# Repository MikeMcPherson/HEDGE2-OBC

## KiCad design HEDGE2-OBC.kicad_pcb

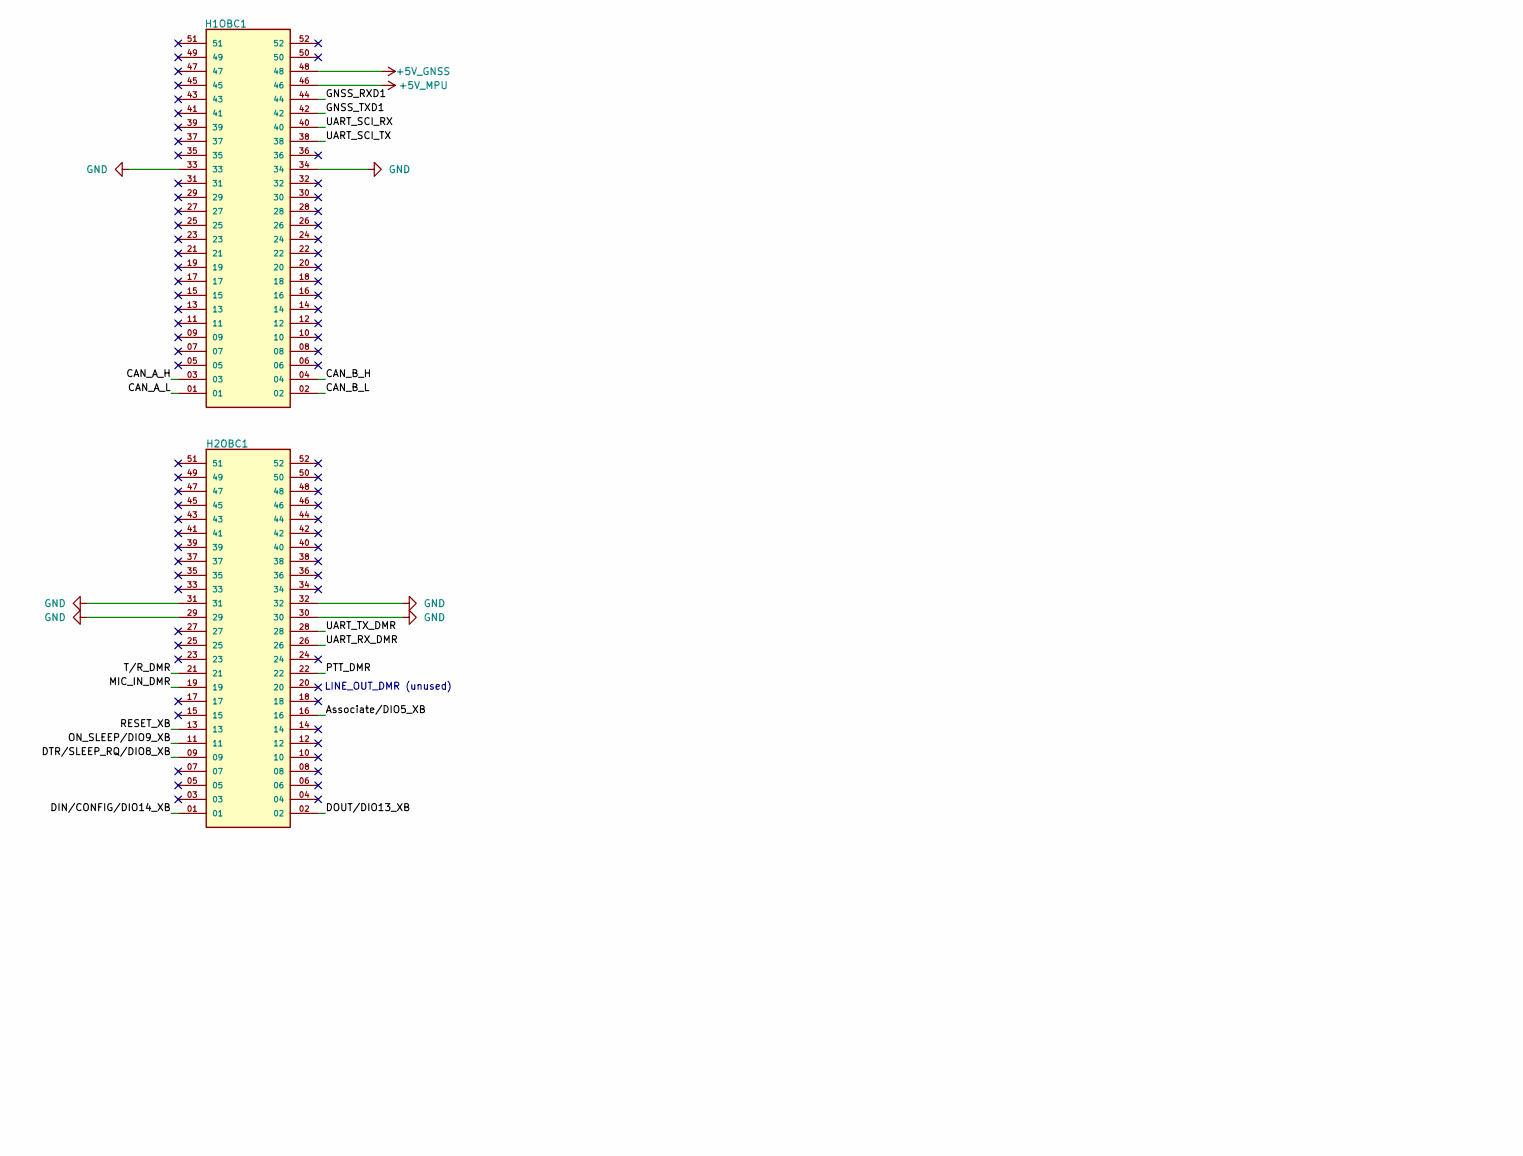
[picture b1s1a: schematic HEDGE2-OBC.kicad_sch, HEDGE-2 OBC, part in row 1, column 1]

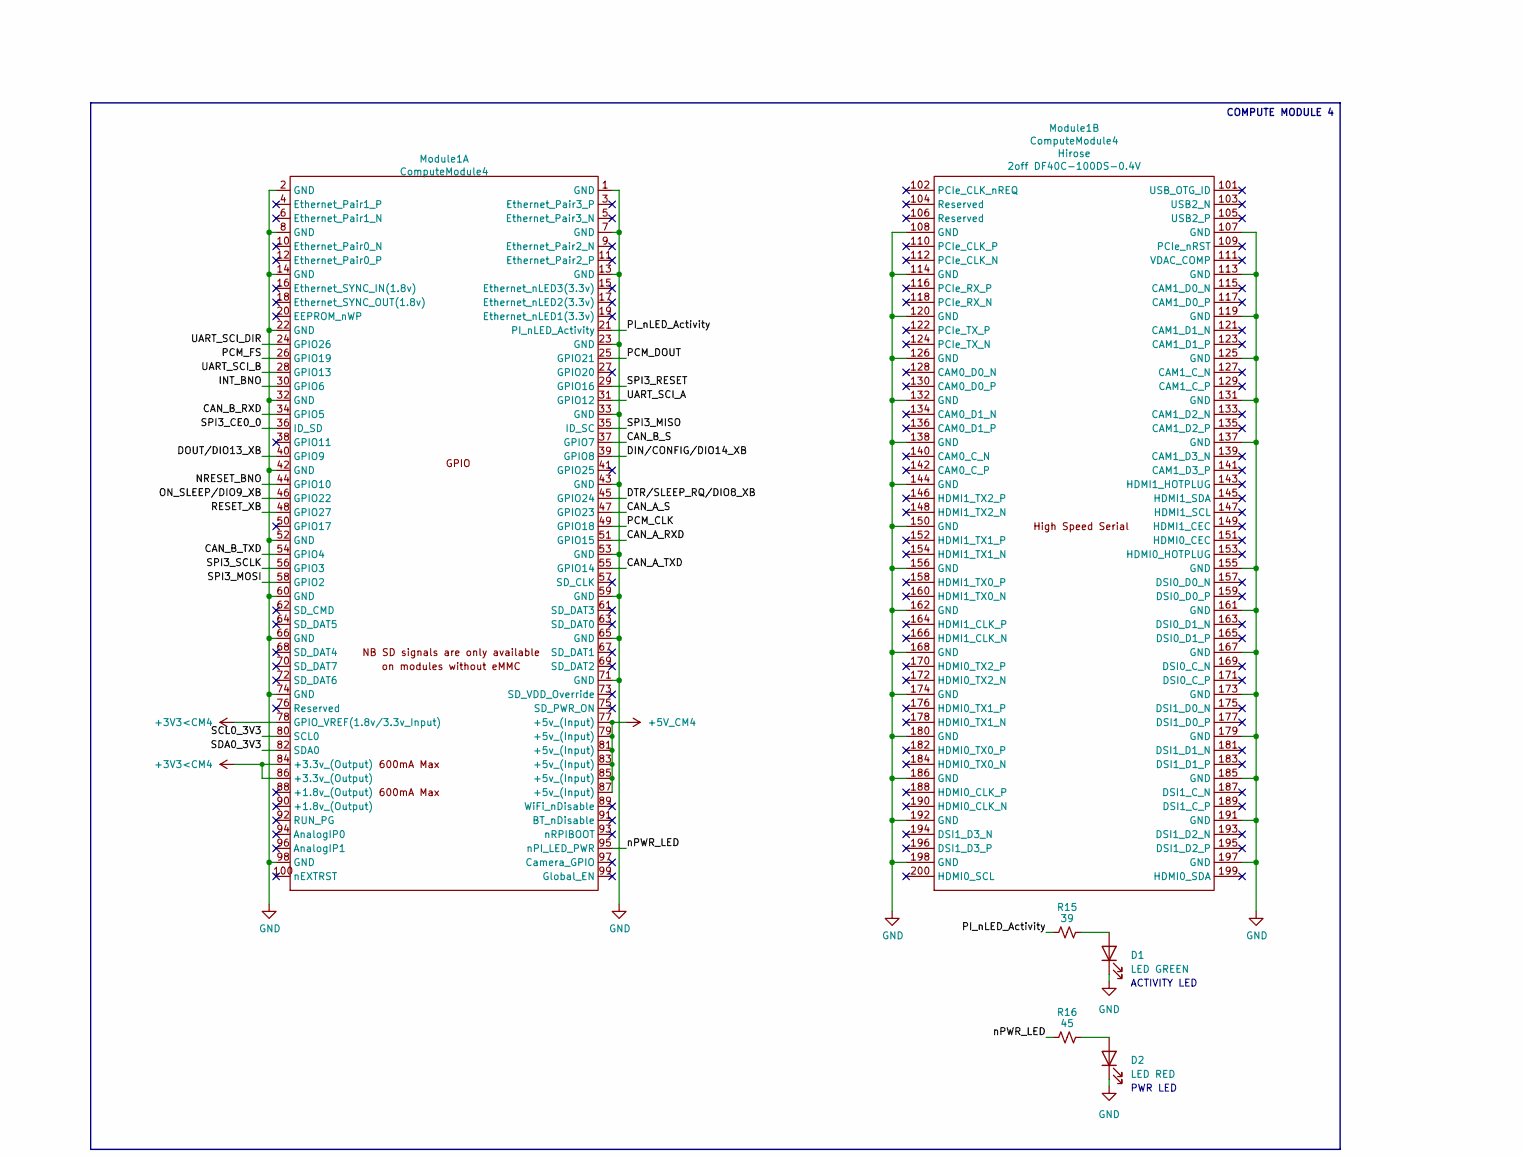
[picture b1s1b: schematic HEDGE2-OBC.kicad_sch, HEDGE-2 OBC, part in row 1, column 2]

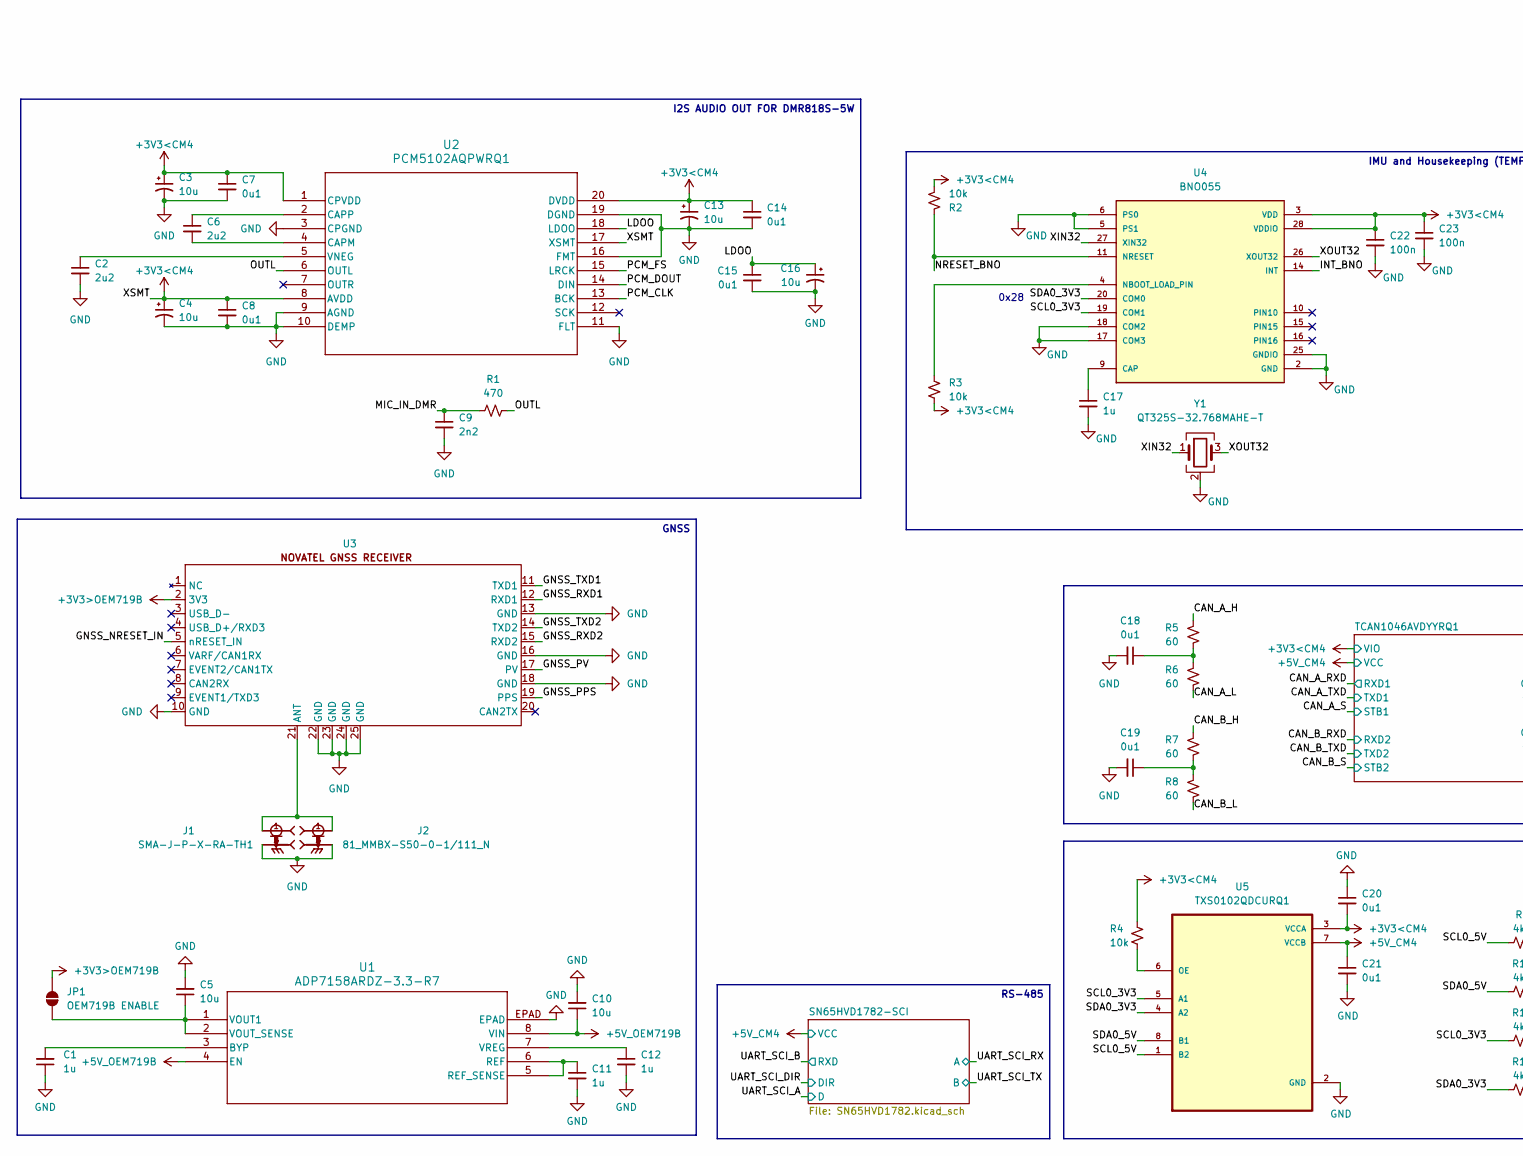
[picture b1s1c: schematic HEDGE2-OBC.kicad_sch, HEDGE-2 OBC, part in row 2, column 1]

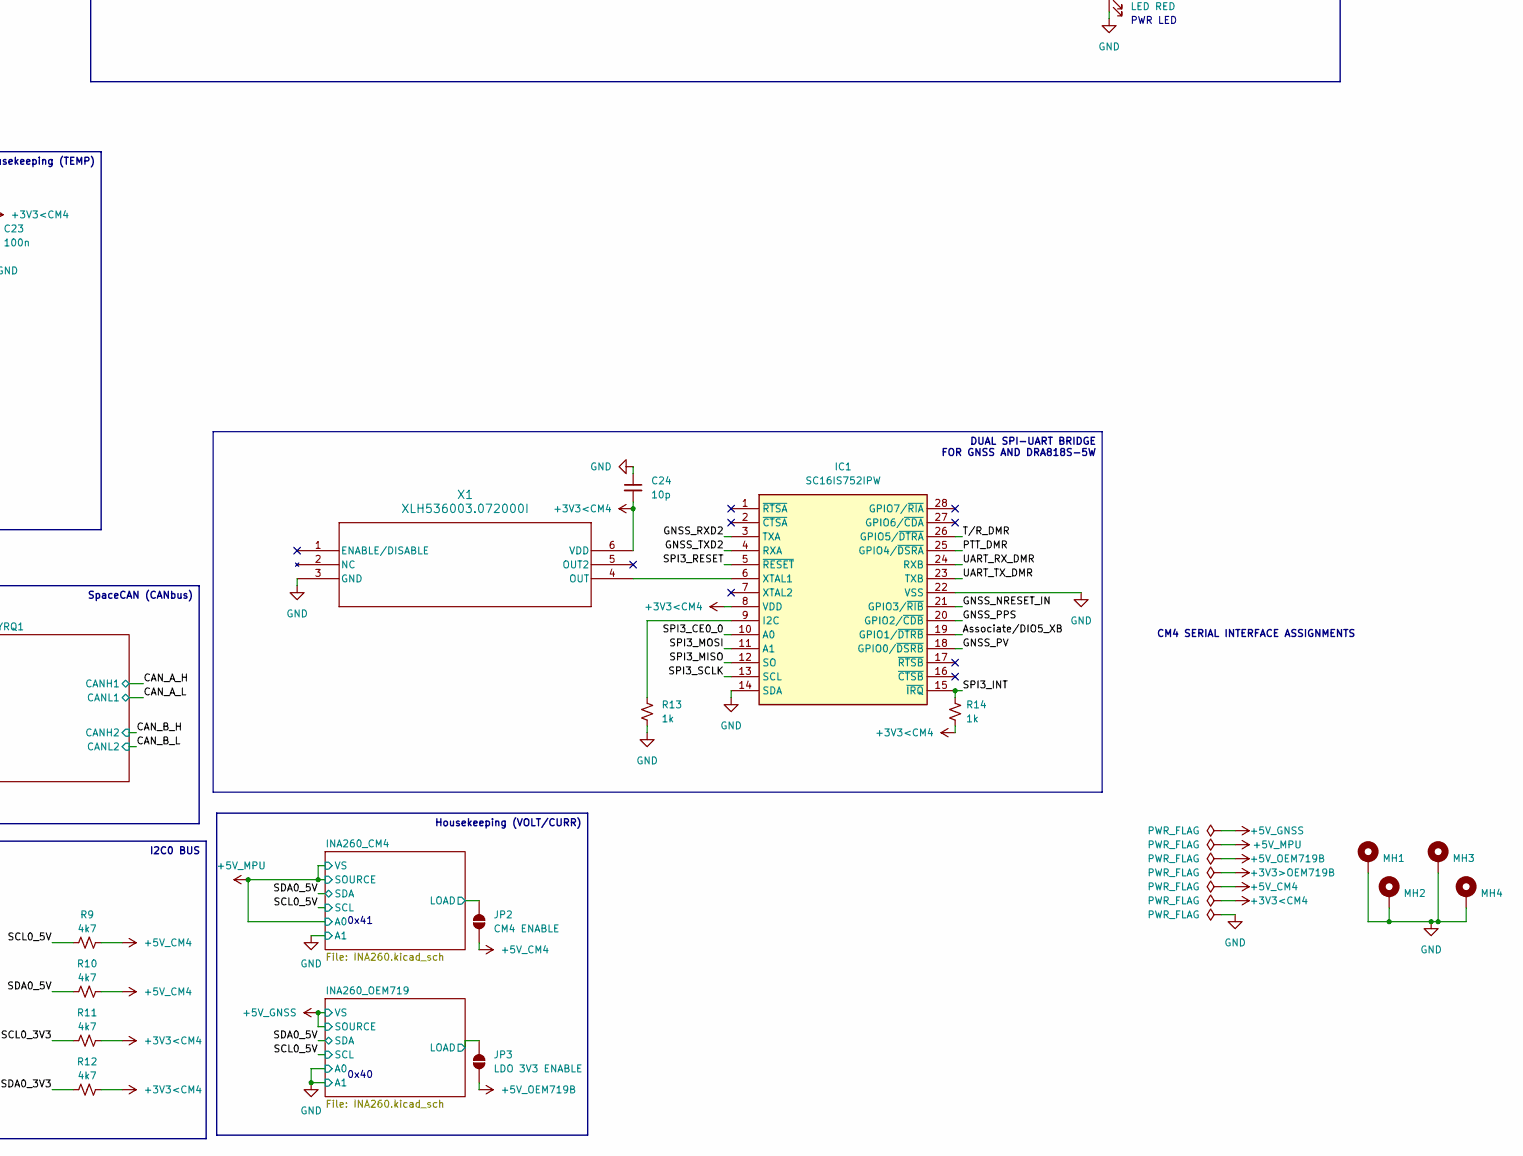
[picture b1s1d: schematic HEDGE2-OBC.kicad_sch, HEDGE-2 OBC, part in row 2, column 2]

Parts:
C1, C11, C12: 1u; C_0805_2012Metric; DigiKey Part Number 1276-1029-1-ND
C2, C6: 2u2; C_0805_2012Metric
C3, C4, C13, C16: 10u; CP_EIA-2012-12_Kemet-R
C5, C10: 10u; C_0805_2012Metric
C7, C8, C14, C15: 0u1; C_0805_2012Metric
C9: 2n2; C_0805_2012Metric
C17: 1u; C_0805_2012Metric
C18, C19, C20, C21: 0u1; C_0805_2012Metric; DigiKey Part Number 720-GA0805Y104JXABT31GCT-ND
C22, C23: 100n; C_0805_2012Metric
C24: 10p; C_0805_2012Metric
D1: LED GREEN; LED_0805_2012Metric; DigiKey Part Number 160-1179-1-ND
D2: LED RED; LED_0805_2012Metric; DigiKey Part Number 160-1427-1-ND
H1OBC1, H2OBC1: Conn_02x26_Odd_Even; SAMTEC_ESQ-126-39-G-D; Manufacturer_Part_Number ESQ-126-39-G-D; Mouser Part Number 200-ESQ12639GD
IC1: SC16IS752IPW; SOP65P640X110-28N; Manufacturer_Part_Number SC16IS752IPW; DigiKey Part Number 568-11944-1-ND
J1: SMA-J-P-X-RA-TH1; SAMTEC_SMA-J-P-X-RA-TH1; PARTREV K; DigiKey Part Number SAM8856-ND
J2: 81_MMBX-S50-0-1/111_N; PARTREV K; DigiKey Part Number 3628-81_MMBX-S50-0-1/111_NMCT-ND
JP1: OEM719B ENABLE; SolderJumper-2_P1.3mm_Open_RoundedPad1.0x1.5mm
JP2: CM4 ENABLE; SolderJumper-2_P1.3mm_Open_RoundedPad1.0x1.5mm
JP3: LDO 3V3 ENABLE; SolderJumper-2_P1.3mm_Open_RoundedPad1.0x1.5mm
MH1, MH2, MH3, MH4: MountingHole_Pad; MountingHole_3.2mm_M3_Pad_Via
Module1: ComputeModule4; MODULE_CM4102008; Part Description 100 Position Connector Receptacle, Cent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; DigiKey Part Number 26-DF40HC(3.0)-100DS-0.4V(51)CT-ND
R1: 470; R_0805_2012Metric
R2, R3: 10k; R_0805_2012Metric
R4: 10k; R_0805_2012Metric; DigiKey Part Number 541-10.0KCCT-ND
R5, R6, R7, R8: 60; R_0805_2012Metric; DigiKey Part Number RMCF0805FT60R4CT-ND
R9, R10, R11, R12: 4k7; R_0805_2012Metric; DigiKey Part Number 541-4131-1-ND
R13, R14: 1k; R_0805_2012Metric
R15: 39; R_0805_2012Metric; DigiKey Part Number P39ACT-ND
R16: 45; R_0805_2012Metric; DigiKey Part Number 311-45.3CRCT-ND
U1: ADP7158ARDZ-3.3-R7; ADP7158ARDZ-3.3-R7_ADI; DigiKey Part Number 505-ADP7158ARDZ-3.3-R7CT-ND
U2: PCM5102AQPWRQ1; PW20; DigiKey Part Number 296-37277-1-ND
U3: OEM719B
U4: BNO055; LGA28R50P4X10_380X520X100; DigiKey_Part_Number 828-1058-1-ND
U5: TXS0102QDCURQ1; SOP50P310X90-8N; DigiKey Part Number 296-37938-1-ND
X1: XLH536003.072000I; SON6_XLH5_5p0x3p2-1p27_REN_REN
Y1: QT325S-32.768MAHE-T; Crystal_SMD_3225-4Pin_3.2x2.5mm

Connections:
+3V3<CM4: C3.1, C4.1, C7.1, C8.1, C13.1, C14.1, C20.2, C22.1, C23.1, C24.2, IC1.8 (VDD), Module1.78 (GPIO_VREF(1.8v/3.3v_Input)), Module1.84 (+3.3v_(Output)), Module1.86 (+3.3v_(Output)), R2.2, R3.2, R4.1, R11.2, R12.2, R14.2, U2.1 (CPVDD), U2.8 (AVDD), U2.17 (XSMT), U2.20 (DVDD), U4.3 (VDD), U4.28 (VDDIO), U5.3 (VCCA), X1.6 (VDD); also elsewhere on the board
+3V3>OEM719B: JP1.2 (B), U3.2 (3V3)
+5V_CM4: C21.1, JP2.1 (A), Module1.77 (+5v_(Input)), Module1.79 (+5v_(Input)), Module1.81 (+5v_(Input)), Module1.83 (+5v_(Input)), Module1.85 (+5v_(Input)), Module1.87 (+5v_(Input)), R9.2, R10.2, U5.7 (VCCB); also elsewhere on the board
+5V_GNSS: H1OBC1.48; also elsewhere on the board
+5V_MPU: H1OBC1.46; also elsewhere on the board
+5V_OEM719B: C10.1, JP3.1 (A), U1.4 (EN), U1.8 (VIN)
/Associate/DIO5_XB: H2OBC1.16, IC1.19 (GPIO1/~DTRB)
/CAN_A_H: H1OBC1.03, R5.1; also elsewhere on the board
/CAN_A_L: H1OBC1.01, R6.2; also elsewhere on the board
/CAN_A_RXD: Module1.51 (GPIO15); also elsewhere on the board
/CAN_A_S: Module1.47 (GPIO23); also elsewhere on the board
/CAN_A_TXD: Module1.55 (GPIO14); also elsewhere on the board
/CAN_B_H: H1OBC1.04, R7.1; also elsewhere on the board
/CAN_B_L: H1OBC1.02, R8.2; also elsewhere on the board
/CAN_B_RXD: Module1.34 (GPIO5); also elsewhere on the board
/CAN_B_S: Module1.37 (GPIO7); also elsewhere on the board
/CAN_B_TXD: Module1.54 (GPIO4); also elsewhere on the board
/DIN/CONFIG/DIO14_XB: H2OBC1.01, Module1.39 (GPIO8)
/DOUT/DIO13_XB: H2OBC1.02, Module1.40 (GPIO9)
/DTR/SLEEP_RQ/DIO8_XB: H2OBC1.09, Module1.45 (GPIO24)
/GNSS_NRESET_IN: IC1.21 (GPIO3/~RIB), U3.5 (nRESET_IN)
/GNSS_PPS: IC1.20 (GPIO2/~CDB), U3.19 (PPS)
/GNSS_PV: IC1.18 (GPIO0/~DSRB), U3.17 (PV)
/GNSS_RXD1: H1OBC1.44, U3.12 (RXD1)
/GNSS_RXD2: IC1.3 (TXA), U3.15 (RXD2)
/GNSS_TXD1: H1OBC1.42, U3.11 (TXD1)
/GNSS_TXD2: IC1.4 (RXA), U3.14 (TXD2)
/INA260_CM4/LOAD: JP2.2 (B); also elsewhere on the board
/INA260_OEM719/LOAD: JP3.2 (B); also elsewhere on the board
/INT_BNO: Module1.30 (GPIO6), U4.14 (INT)
/LDOO: C15.1, C16.1, U2.18 (LDOO)
/MIC_IN_DMR: C9.1, H2OBC1.19, R1.1
/NRESET_BNO: Module1.44 (GPIO10), R2.1, U4.11 (NRESET)
/ON_SLEEP/DIO9_XB: H2OBC1.11, Module1.46 (GPIO22)
/OUTL: R1.2, U2.6 (OUTL)
/PCM_CLK: Module1.49 (GPIO18), U2.13 (BCK)
/PCM_DOUT: Module1.25 (GPIO21), U2.14 (DIN)
/PCM_FS: Module1.26 (GPIO19), U2.15 (LRCK)
/PI_nLED_Activity: Module1.21 (PI_nLED_Activity), R15.1
/PTT_DMR: H2OBC1.22, IC1.25 (GPIO4/~DSRA)
/RESET_XB: H2OBC1.13, Module1.48 (GPIO27)
/SCL0_3V3: Module1.80 (SCL0), R11.1, U4.19 (COM1), U5.5 (A1)
/SCL0_5V: R9.1, U5.1 (B2); also elsewhere on the board
/SDA0_3V3: Module1.82 (SDA0), R12.1, U4.20 (COM0), U5.4 (A2)
/SDA0_5V: R10.1, U5.8 (B1); also elsewhere on the board
/SPI3_CE0_0: IC1.10 (A0), Module1.36 (ID_SD)
/SPI3_INT: IC1.15 (~IRQ), R14.1
/SPI3_MISO: IC1.12 (SO), Module1.35 (ID_SC)
/SPI3_MOSI: IC1.11 (A1), Module1.58 (GPIO2)
/SPI3_RESET: IC1.5 (~RESET), Module1.29 (GPIO16)
/SPI3_SCLK: IC1.13 (SCL), Module1.56 (GPIO3)
/T/R_DMR: H2OBC1.21, IC1.26 (GPIO5/~DTRA)
/UART_RX_DMR: H2OBC1.26, IC1.24 (RXB)
/UART_SCI_A: Module1.31 (GPIO12); also elsewhere on the board
/UART_SCI_B: Module1.28 (GPIO13); also elsewhere on the board
/UART_SCI_DIR: Module1.24 (GPIO26); also elsewhere on the board
/UART_SCI_RX: H1OBC1.40; also elsewhere on the board
/UART_SCI_TX: H1OBC1.38; also elsewhere on the board
/UART_TX_DMR: H2OBC1.28, IC1.23 (TXB)
/XIN32: U4.27 (XIN32), Y1.1
/XOUT32: U4.26 (XOUT32), Y1.3
/nPWR_LED: Module1.95 (nPI_LED_PWR), R16.1
GND: C1.1, C2.2, C3.2, C4.2, C5.2, C7.2, C8.2, C9.2, C10.2, C11.2, C12.2, C13.2, C14.2, C15.2, C16.2, C17.2, C18.2, C19.2, C20.1, C21.2, C22.2, C23.2, C24.1, D1.1 (K), D2.1 (K), H1OBC1.33, H1OBC1.34, H2OBC1.29, H2OBC1.30, H2OBC1.31, H2OBC1.32, IC1.14 (SDA), IC1.22 (VSS), J1.2, J1.3, J1.4, J1.5, J2.2, J2.3, J2.4, J2.5, MH1.1, MH2.1, MH3.1, MH4.1, Module1.1 (GND), Module1.2 (GND), Module1.7 (GND), Module1.8 (GND), Module1.13 (GND), Module1.14 (GND), Module1.22 (GND), Module1.23 (GND), Module1.32 (GND), Module1.33 (GND), Module1.42 (GND), Module1.43 (GND), Module1.52 (GND), Module1.53 (GND), Module1.59 (GND), Module1.60 (GND), Module1.65 (GND), Module1.66 (GND), Module1.71 (GND), Module1.74 (GND), Module1.98 (GND), Module1.107 (GND), Module1.108 (GND), Module1.113 (GND), Module1.114 (GND), Module1.119 (GND), Module1.120 (GND), Module1.125 (GND), Module1.126 (GND), Module1.131 (GND), Module1.132 (GND), Module1.137 (GND), Module1.138 (GND), Module1.144 (GND), Module1.150 (GND), Module1.155 (GND), Module1.156 (GND), Module1.161 (GND), Module1.162 (GND), Module1.167 (GND), Module1.168 (GND), Module1.173 (GND), Module1.174 (GND), Module1.179 (GND), Module1.180 (GND), Module1.185 (GND), Module1.186 (GND), Module1.191 (GND), Module1.192 (GND), Module1.197 (GND), Module1.198 (GND), R13.2, U1.EPAD, U2.3 (CPGND), U2.9 (AGND), U2.10 (DEMP), U2.11 (FLT), U2.16 (FMT), U2.19 (DGND), U3.10 (GND), U3.13 (GND), U3.16 (GND), U3.18 (GND), U3.22 (GND), U3.23 (GND), U3.24 (GND), U3.25 (GND), U4.2 (GND), U4.5 (PS1), U4.6 (PS0), U4.17 (COM3), U4.18 (COM2), U4.25 (GNDIO), U5.2 (GND), X1.3 (GND), Y1.2 (G), Y1.4 (G); also elsewhere on the board
unnamed: C18.1, R5.2, R6.1
unnamed: C19.1, R7.2, R8.1
unnamed: D1.2 (A), R15.2
unnamed: D2.2 (A), R16.2
unnamed: IC1.9 (I2C), R13.1
unnamed: IC1.6 (XTAL1), X1.4 (OUT)
unnamed: C5.1, JP1.1 (A), U1.1 (VOUT1), U1.2 (VOUT_SENSE)
unnamed: C1.2, U1.3 (BYP)
unnamed: C11.1, U1.5 (REF_SENSE), U1.6 (REF)
unnamed: C12.1, U1.7 (VREG)
unnamed: C6.2, U2.4 (CAPM)
unnamed: C6.1, U2.2 (CAPP)
unnamed: C2.1, U2.5 (VNEG)
unnamed: J1.1, J2.1, U3.21 (ANT)
unnamed: C17.1, U4.9 (CAP)
unnamed: R3.1, U4.4 (NBOOT_LOAD_PIN)
unnamed: R4.2, U5.6 (OE)

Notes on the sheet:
0x28
PWR LED
CM4 SERIAL INTERFACE ASSIGNMENTS
0x41
0x40
ACTIVITY LED
LINE_OUT_DMR (unused)
I2S AUDIO OUT FOR DMR818S-5W
Housekeeping (VOLT/CURR)
GNSS
RS-485
IMU and Housekeeping (TEMP)
DUAL SPI-UART BRIDGE FOR GNSS AND DRA818S-5W
I2C0 BUS
SpaceCAN (CANbus)
COMPUTE MODULE 4

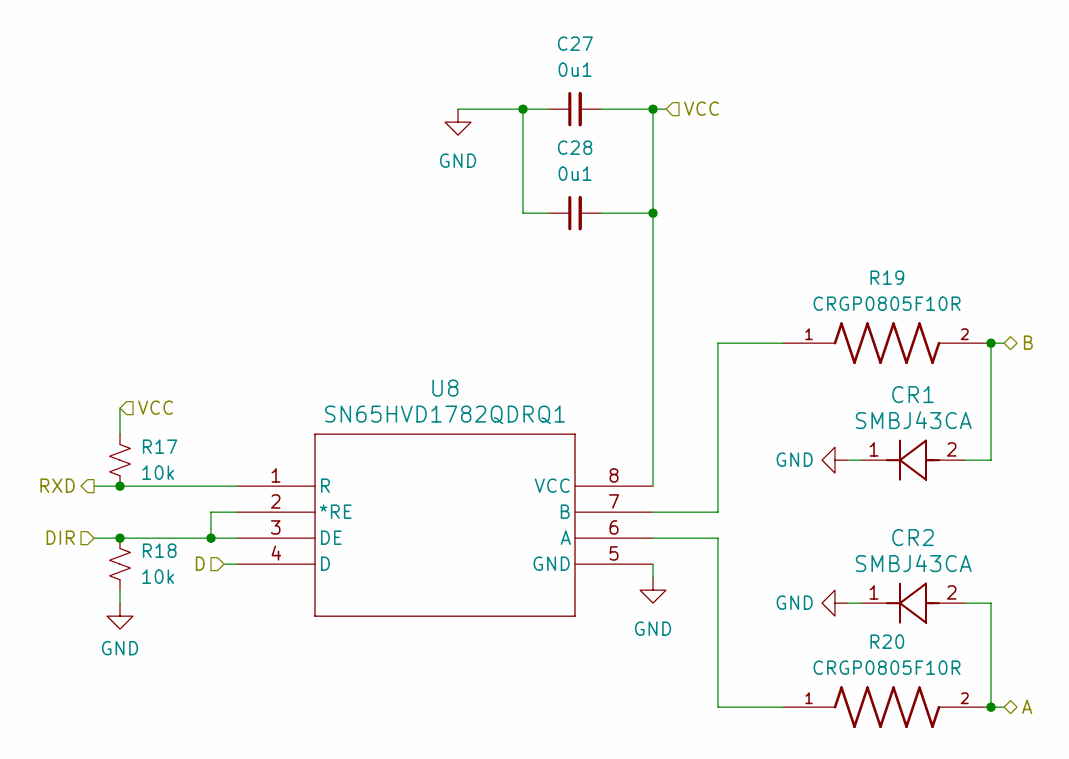
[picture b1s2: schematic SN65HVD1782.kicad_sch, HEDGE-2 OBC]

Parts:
C27, C28: 0u1; C_0805_2012Metric; DigiKey Part Number 720-GA0805Y104JXABT31GCT-ND
CR1, CR2: SMBJ43CA; SMBJSeries_LTF; DigiKey Part Number SMBJ43CALFCT-ND
R17, R18: 10k; R_0805_2012Metric; DigiKey Part Number 541-10.0KCCT-ND
R19, R20: CRGP0805F10R; RESC2012X65N; DigiKey Part Number A130453CT-ND
U8: SN65HVD1782QDRQ1; D8_TEX; DigiKey Part Number 296-43745-1-ND

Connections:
+5V_CM4: C27.2, C28.2, R17.1, U8.8 (VCC); also elsewhere on the board
/UART_SCI_A: U8.4 (D); also elsewhere on the board
/UART_SCI_B: R17.2, U8.1 (R); also elsewhere on the board
/UART_SCI_DIR: R18.1, U8.2 (*RE), U8.3 (DE); also elsewhere on the board
/UART_SCI_RX: CR2.2, R20.2; also elsewhere on the board
/UART_SCI_TX: CR1.2, R19.2; also elsewhere on the board
GND: C27.1, C28.1, CR1.1, CR2.1, R18.2, U8.5 (GND); also elsewhere on the board
unnamed: R20.1, U8.6 (A)
unnamed: R19.1, U8.7 (B)

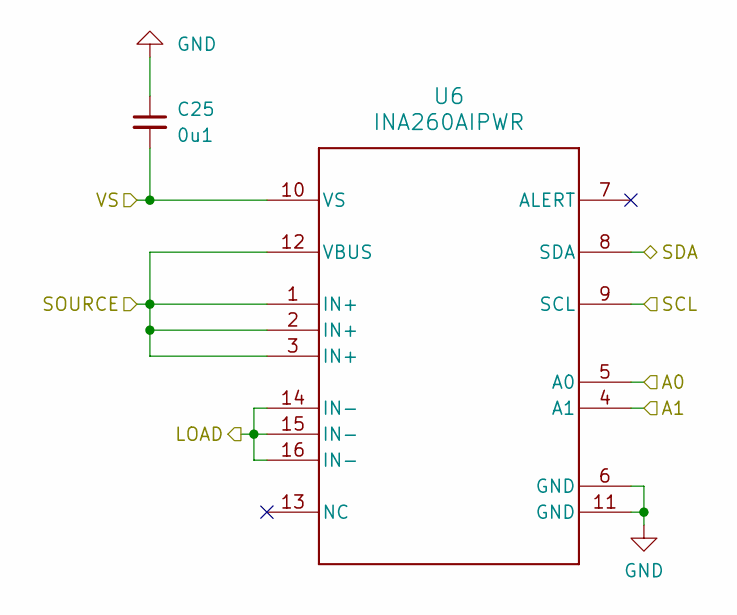
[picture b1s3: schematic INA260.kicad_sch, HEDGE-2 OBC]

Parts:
C25: 0u1; C_0805_2012Metric; DigiKey Part Number 720-GA0805Y104JXABT31GCT-ND
U6: INA260AIPWR; PW0016A_L; DigiKey Part Number 296-45218-5-ND

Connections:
+5V_MPU: C25.2, U6.1 (IN+), U6.2 (IN+), U6.3 (IN+), U6.5 (A0), U6.10 (VS), U6.12 (VBUS); also elsewhere on the board
/INA260_CM4/LOAD: U6.14 (IN-), U6.15 (IN-), U6.16 (IN-); also elsewhere on the board
/SCL0_5V: U6.9 (SCL); also elsewhere on the board
/SDA0_5V: U6.8 (SDA); also elsewhere on the board
GND: C25.1, U6.4 (A1), U6.6 (GND), U6.11 (GND); also elsewhere on the board

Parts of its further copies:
C26: 0u1; C_0805_2012Metric; DigiKey Part Number 720-GA0805Y104JXABT31GCT-ND
U7: INA260AIPWR; PW0016A_L; DigiKey Part Number 296-45218-5-ND

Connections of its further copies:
+5V_GNSS: C26.2, U7.1 (IN+), U7.2 (IN+), U7.3 (IN+), U7.10 (VS), U7.12 (VBUS); also elsewhere on the board
/INA260_OEM719/LOAD: U7.14 (IN-), U7.15 (IN-), U7.16 (IN-); also elsewhere on the board
/SCL0_5V: U7.9 (SCL); also elsewhere on the board
/SDA0_5V: U7.8 (SDA); also elsewhere on the board
GND: C26.1, U7.4 (A1), U7.5 (A0), U7.6 (GND), U7.11 (GND); also elsewhere on the board

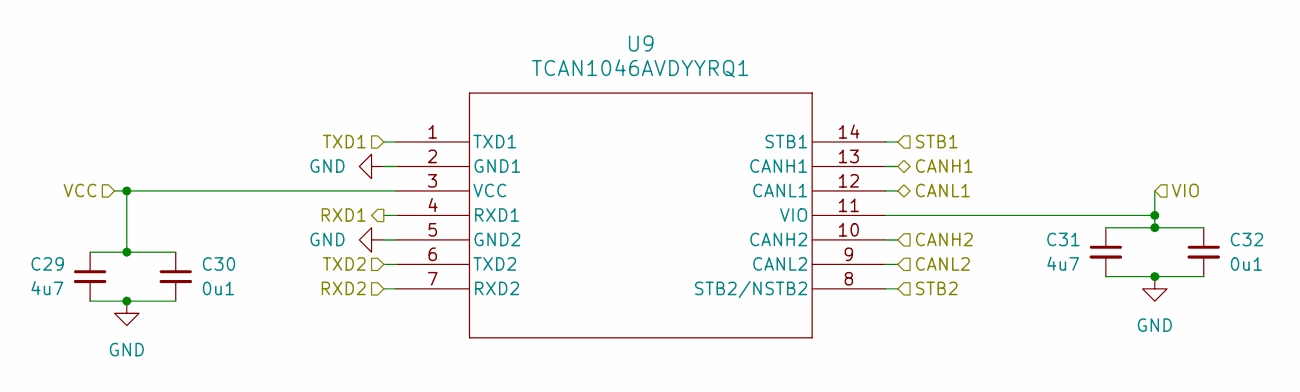
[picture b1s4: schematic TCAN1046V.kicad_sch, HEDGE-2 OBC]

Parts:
C29, C31: 4u7; C_0805_2012Metric; DigiKey Part Number 490-GRT21BC71H475KE13LCT-ND
C30, C32: 0u1; C_0805_2012Metric; DigiKey Part Number 720-GA0805Y104JXABT31GCT-ND
U9: TCAN1046AVDYYRQ1; SOT23_DYY_TEX; DigiKey Part Number 296-TCAN1046AVDYYRQ1CT-ND

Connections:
+3V3<CM4: C31.1, C32.1, U9.11 (VIO); also elsewhere on the board
+5V_CM4: C29.1, C30.1, U9.3 (VCC); also elsewhere on the board
/CAN_A_H: U9.13 (CANH1); also elsewhere on the board
/CAN_A_L: U9.12 (CANL1); also elsewhere on the board
/CAN_A_RXD: U9.4 (RXD1); also elsewhere on the board
/CAN_A_S: U9.14 (STB1); also elsewhere on the board
/CAN_A_TXD: U9.1 (TXD1); also elsewhere on the board
/CAN_B_H: U9.10 (CANH2); also elsewhere on the board
/CAN_B_L: U9.9 (CANL2); also elsewhere on the board
/CAN_B_RXD: U9.7 (RXD2); also elsewhere on the board
/CAN_B_S: U9.8 (STB2/NSTB2); also elsewhere on the board
/CAN_B_TXD: U9.6 (TXD2); also elsewhere on the board
GND: C29.2, C30.2, C31.2, C32.2, U9.2 (GND1), U9.5 (GND2); also elsewhere on the board

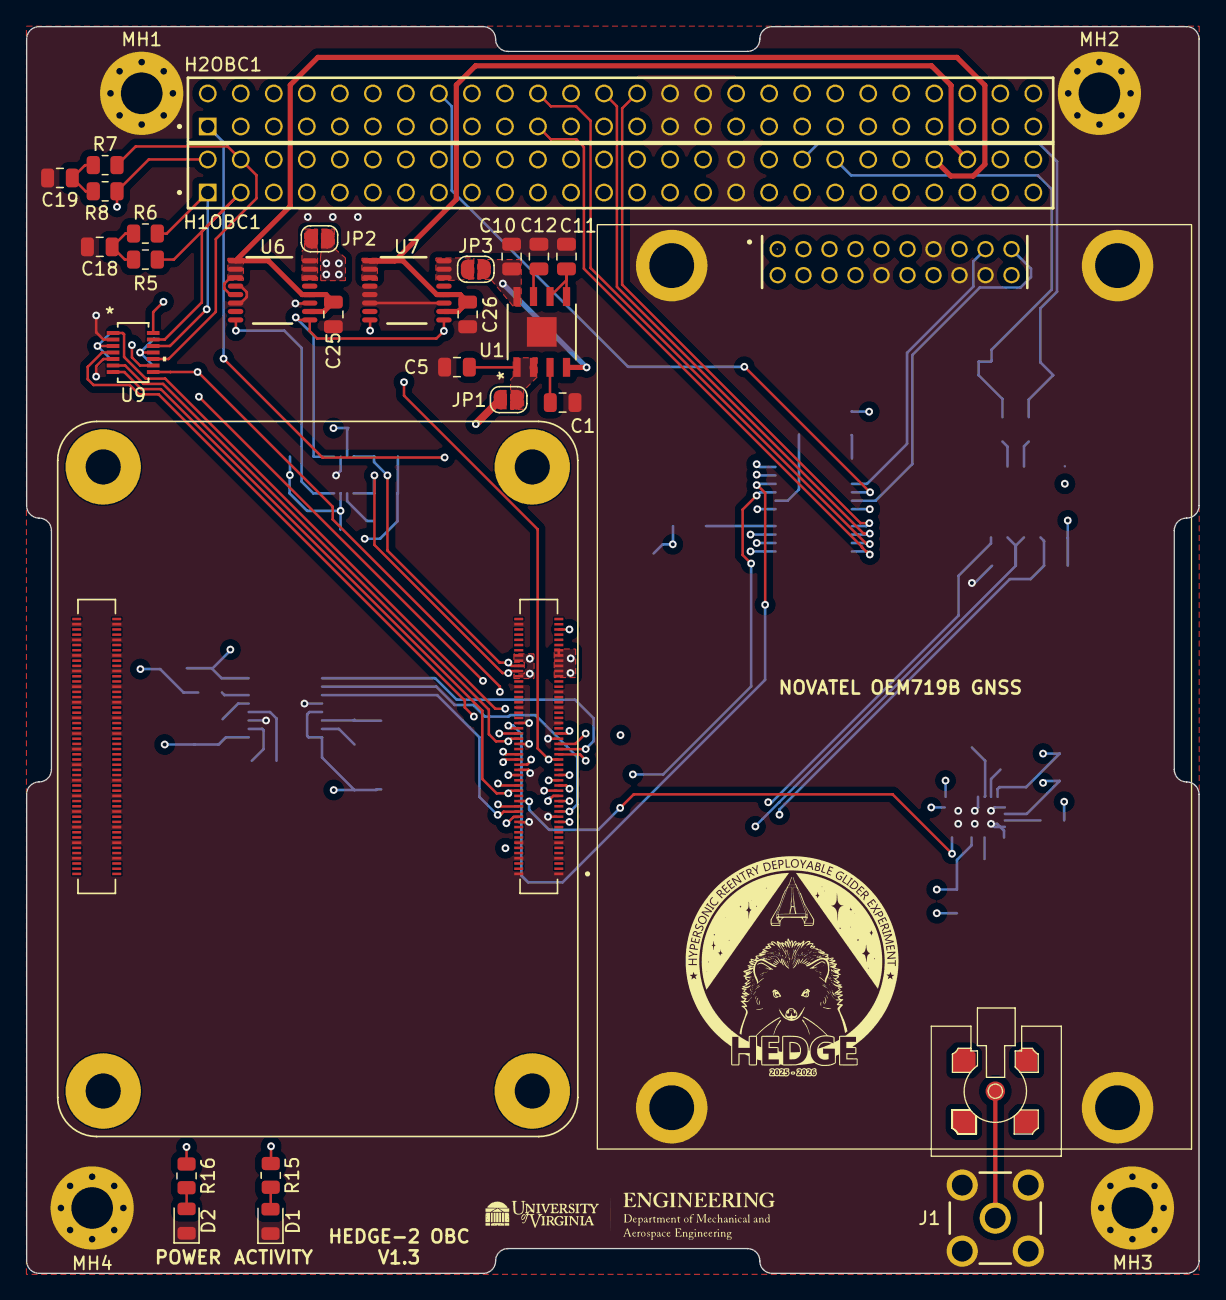
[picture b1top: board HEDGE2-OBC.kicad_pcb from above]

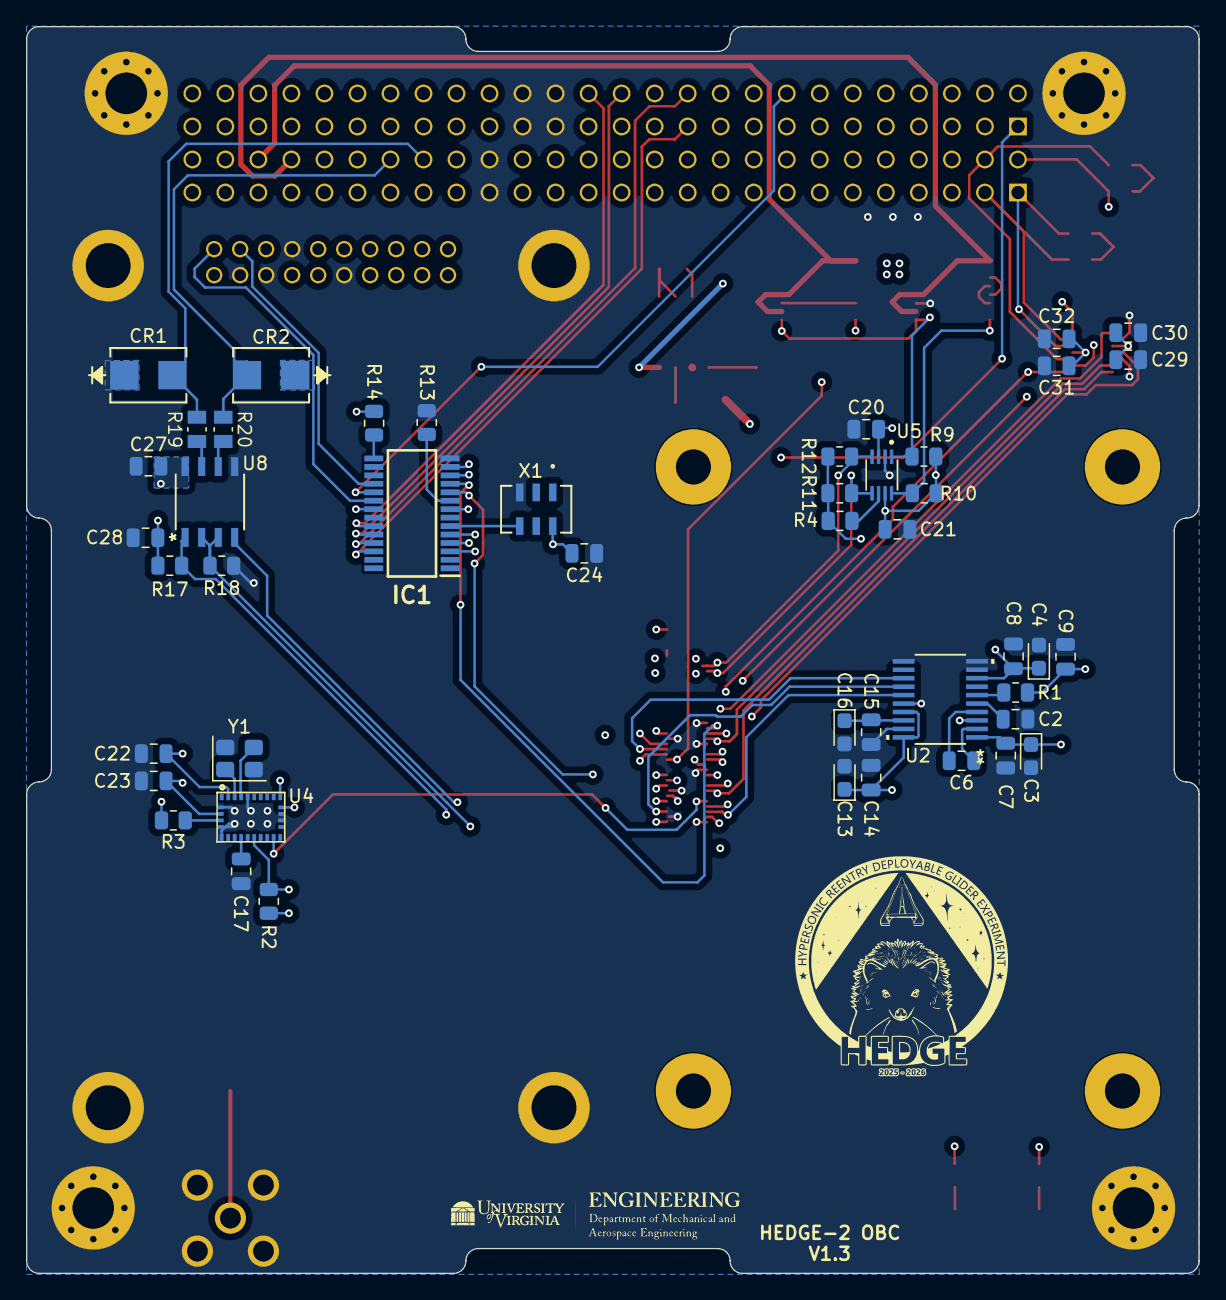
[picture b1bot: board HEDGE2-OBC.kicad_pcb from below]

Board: 4 copper layers, 90.2 x 95.9 mm, 79 parts (46 on the bottom side), 82 nets.

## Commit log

2025-09-21 Start new PCB layout for second test article
2025-09-21 Begin v1.1 layout
2025-09-21 Add power zones on In1 and In2
2025-09-22 Rework Novatel OEM719B symbol and footprint
2025-09-22 Layout PCB; update footprints with 3D models
2025-09-23 Continue PCB layout
2025-09-25 Continue layout
2025-10-01 ERC/DRC
2025-10-02 Fix MMBX footprint; resolve ERC/DRC
2025-10-02 Layout complete
2025-10-02 Final layout, submitted to DFM
2025-10-03 Add functional block labels to schematic
2025-10-04 Online DFM satisfactory
2025-10-06 Verify CM4 and OEM710B footprints and clearances; add mounting hardware
2025-10-06 Remove spurious STEP file
2025-10-07 Arbitrary change for demo purposes
2025-12-07 Fix TCAN power supply swap
2026-01-11 Prepare for merge
2026-01-11 Add cap to 3V3 LDO output; add solder jumpers; change 3V3 routing
2026-01-11 Fix solder mask on Pi connectors
2026-01-11 Clean up CM4 routing
2026-01-28 Add PCM5102A I2S audio output for APRS radio
2026-01-29 Add PCM and SPI UART; begin layout update
2026-01-29 Continue layout update
2026-02-02 Add IMU; eliminate environmental sensor; finish layout
2026-03-06 Final cleanup
2026-03-08 Fix JP3 footprint reversal; start CAD for CM4 spacers
2026-03-08 Fix GNSS antenna grounding problem
2026-04-15 3D-printed spacer for CM4; correct UART pins in table
